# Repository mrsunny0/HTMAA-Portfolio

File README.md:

# George HTMAA Project Portfolio

[How to make almost anything](http://fab.cba.mit.edu/classes/MAS.863)

[Personal 
project page](http://fab.cba.mit.edu/classes/863.17/CBA/people/George%20Sun/index.html)

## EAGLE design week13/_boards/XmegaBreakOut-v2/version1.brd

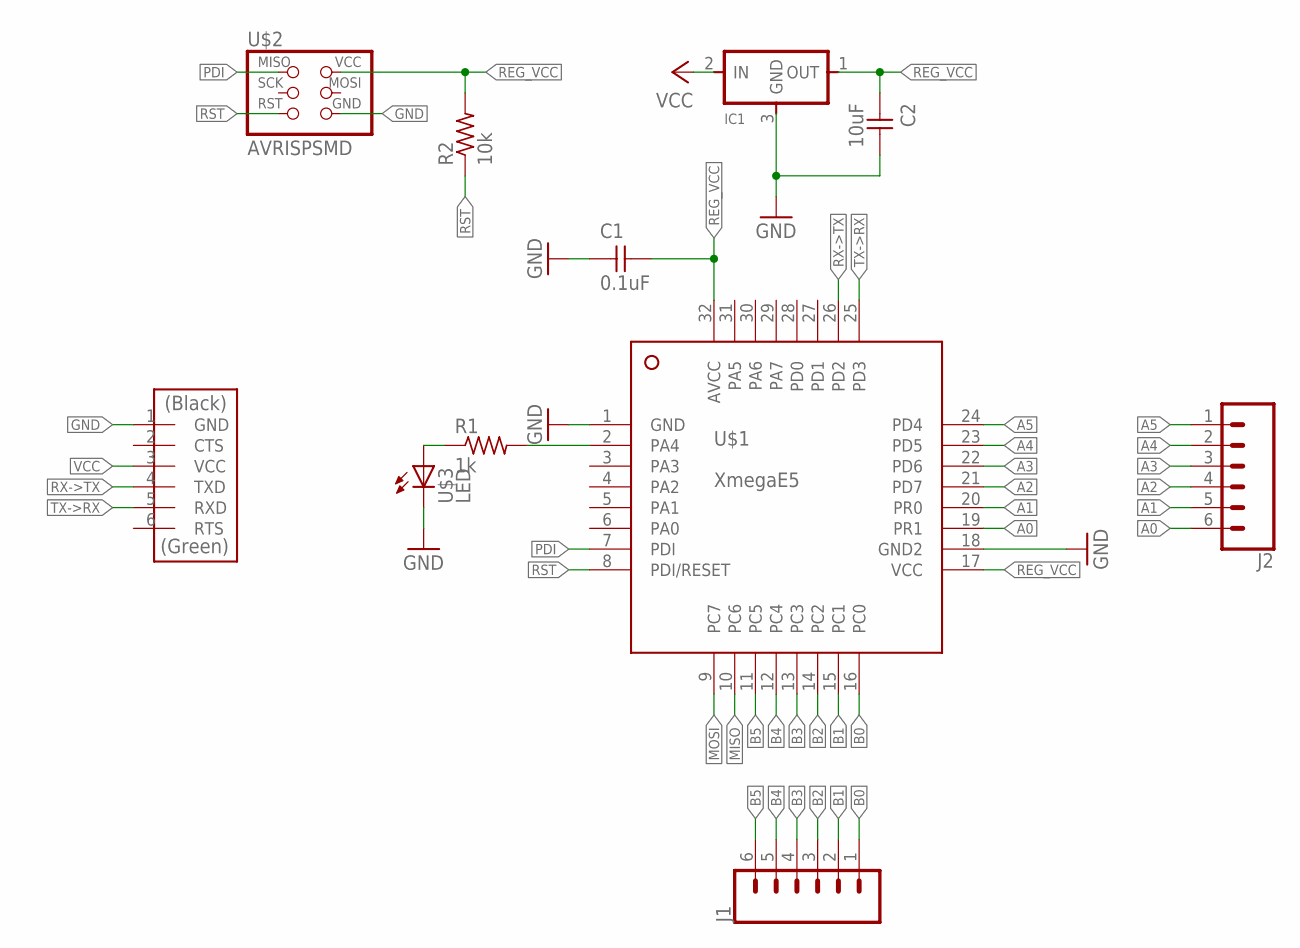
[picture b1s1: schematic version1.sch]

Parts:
C1: 0.1uF; C1206FAB
C2: 10uF; C1206FAB
IC1: REGULATORSOT23; SOT23
J1, J2: CONN_06SMD_MALE; 1X06_SMD_MALE
R1: 1k; R1206FAB
R2: 10k; R1206FAB
U$1: XmegaE5; QFP80P900X900X120-32N
U$2: AVRISPSMD; 2X03SMD
U$3: LED; LED1206FAB
U$4: FTDI-SMD-HEADER; 1X06SMD

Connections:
A0: J2.6, U$1.19 (PR1)
A1: J2.5, U$1.20 (PR0)
A2: J2.4, U$1.21 (PD7)
A3: J2.3, U$1.22 (PD6)
A4: J2.2, U$1.23 (PD5)
A5: J2.1, U$1.24 (PD4)
B0: J1.1, U$1.16 (PC0)
B1: J1.2, U$1.15 (PC1)
B2: J1.3, U$1.14 (PC2)
B3: J1.4, U$1.13 (PC3)
B4: J1.5, U$1.12 (PC4)
B5: J1.6, U$1.11 (PC5)
GND: C1.1, C2.2, IC1.3 (GND), U$1.1 (GND), U$1.18 (GND2), U$2.6 (GND), U$3.2 (C), U$4.1 (GND)
MISO: U$1.10 (PC6)
MOSI: U$1.9 (PC7)
unnamed: R1.2, U$1.2 (PA4)
unnamed: R1.1, U$3.1 (A)
PDI: U$1.7 (PDI), U$2.1 (MISO)
REG_VCC: C1.2, C2.1, IC1.1 (OUT), R2.2, U$1.17 (VCC), U$1.32 (AVCC), U$2.2 (VCC)
RST: R2.1, U$1.8 (PDI/RESET), U$2.5 (RST)
RX->TX: U$1.26 (PD2), U$4.4 (TXD)
TX->RX: U$1.25 (PD3), U$4.5 (RXD)
VCC: IC1.2 (IN), U$4.3 (VCC)

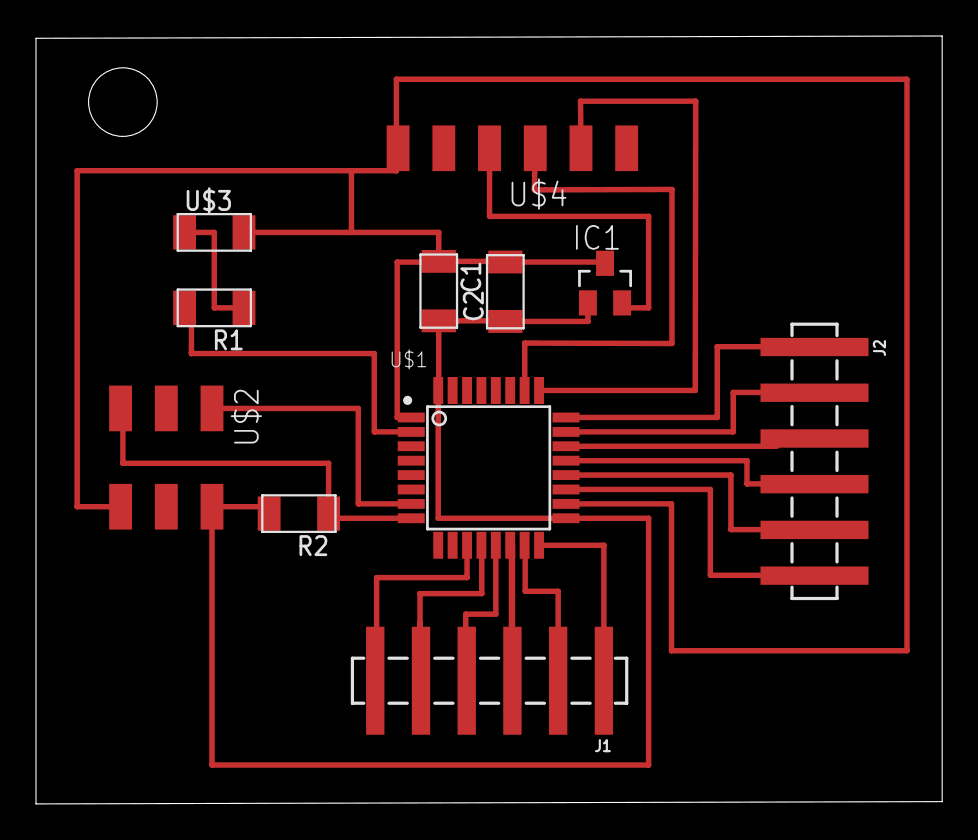
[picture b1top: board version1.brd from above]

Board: 2 copper layers, 50.3 x 42.7 mm, 11 parts (0 on the bottom side), 21 nets.

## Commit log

2019-12-27 changed names, hrefs to other pages now work
2019-12-27 created separate gh-pages branch
2020-05-08 Adding year copyright using js

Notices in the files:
parts and their libraries:
SparkFun-Connectors: Licensing: Creative Commons ShareAlike 4.0 International - https://creativecommons.org/licenses/by-sa/4.0
